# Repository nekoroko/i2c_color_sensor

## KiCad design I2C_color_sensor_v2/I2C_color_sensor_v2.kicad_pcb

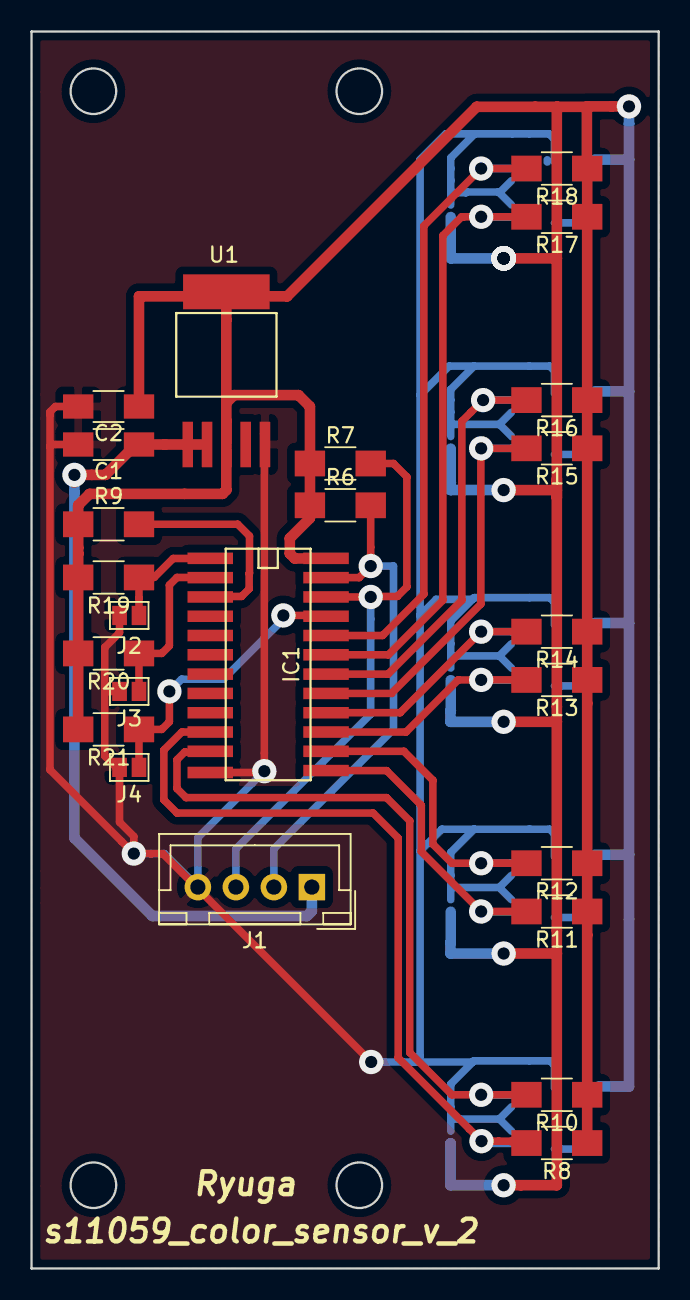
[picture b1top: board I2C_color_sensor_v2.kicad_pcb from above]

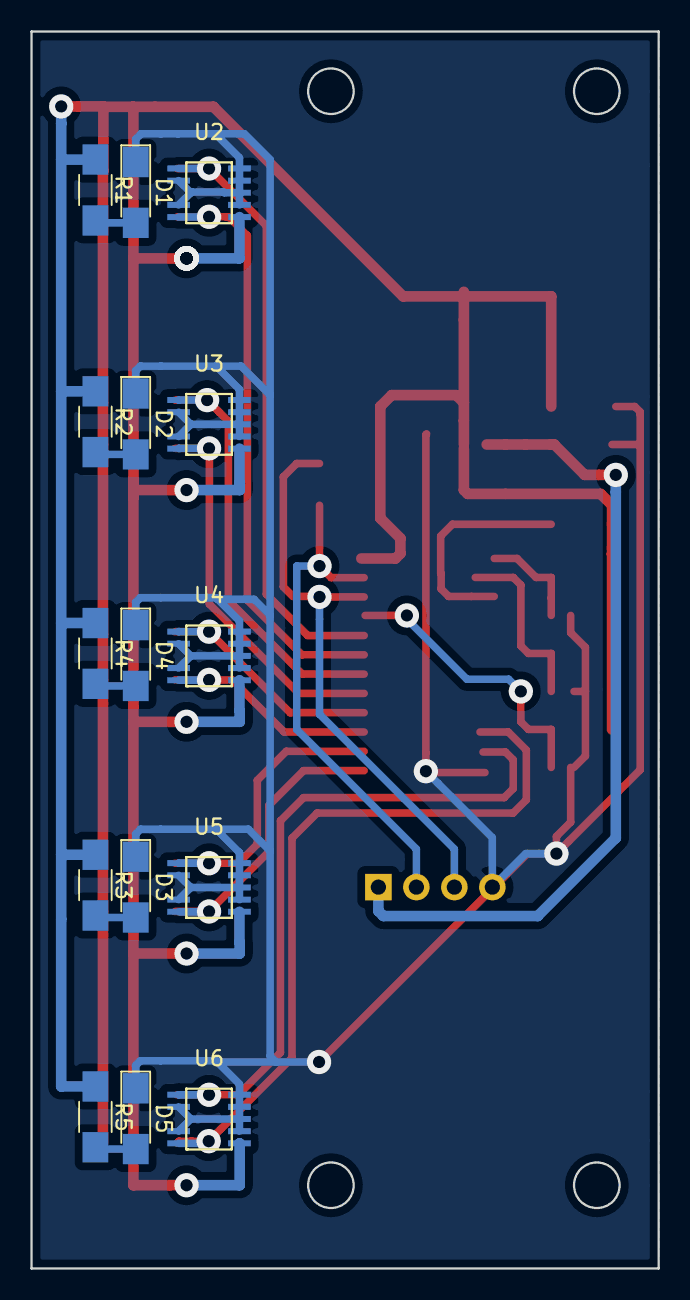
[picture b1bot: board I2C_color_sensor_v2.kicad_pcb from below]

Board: 2 copper layers, 41.3 x 81.4 mm, 39 parts (15 on the bottom side), 24 nets.

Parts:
C1, C2: C; C_1206_HandSoldering
D1, D2, D3, D4, D5: LED; LED_1206_HandSoldering
IC1: PCA9547D,112; SOIC-24
J1: Conn_01x04; JST_XH_B04B-XH-A_04x2.50mm_Straight
J2, J3, J4: GS2
R1, R2, R3, R4, R5, R6, R7, R8, R9, R10, R11, R12, R13, R14, R15, R16, R17, R18, R19, R20, R21: R; R_1206_HandSoldering
U1: PQ033EZ1HZ; PQ033EZH1HZ
U2, U3, U4, U5, U6: S11059; S11059_SMD

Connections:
+3V3: C2.1, IC1.24, R1.1, R2.1, R3.1, R4.1, R5.1, R6.1, R7.1, R8.1, R9.1, R10.1, R11.1, R12.1, R13.1, R14.1, R15.1, R16.1, R17.1, R18.1, R19.2, R20.2, R21.2, U1.3, U2.1, U3.1, U4.1, U5.1, U6.1
+5V: C1.1, J1.1, U1.1, U1.2
A0: IC1.1, J2.1, R19.1
A1: IC1.2, J3.1, R20.1
A2: IC1.21, J4.1, R21.1
GND: C1.2, C2.2, D1.1, D2.1, D3.1, D4.1, D5.1, IC1.12, J1.4, J2.2, J3.2, J4.2, U1.5, U2.2, U2.3, U2.4, U2.5, U2.7, U2.9, U3.2, U3.3, U3.4, U3.5, U3.7, U3.9, U4.2, U4.3, U4.4, U4.5, U4.7, U4.9, U5.2, U5.3, U5.4, U5.5, U5.7, U5.9, U6.2, U6.3, U6.4, U6.5, U6.7, U6.9
unnamed: D1.2, R1.2
unnamed: D2.2, R2.2
unnamed: D3.2, R3.2
unnamed: D4.2, R4.2
unnamed: D5.2, R5.2
unnamed: IC1.3, R9.2
scl: IC1.22, J1.3, R7.2
scl3: IC1.11, R10.2, U6.6
scl4: IC1.14, R12.2, U5.6
scl5: IC1.16, R14.2, U4.6
scl6: IC1.18, R16.2, U3.6
scl7: IC1.20, R18.2, U2.6
sda: IC1.23, J1.2, R6.2
sda3: IC1.10, R8.2, U6.10
sda4: IC1.13, R11.2, U5.10
sda5: IC1.15, R13.2, U4.10
sda6: IC1.17, R15.2, U3.10
sda7: IC1.19, R17.2, U2.10

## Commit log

2019-06-14 [remove]不要なファイルの削除
    図や未提出のガーバーデータの削除
